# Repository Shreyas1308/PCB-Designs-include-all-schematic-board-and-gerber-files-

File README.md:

# PCB-Designs-include-all-schematic-board-and-gerber-files-
All file including Gerber(.zip), schematic and board are included here.

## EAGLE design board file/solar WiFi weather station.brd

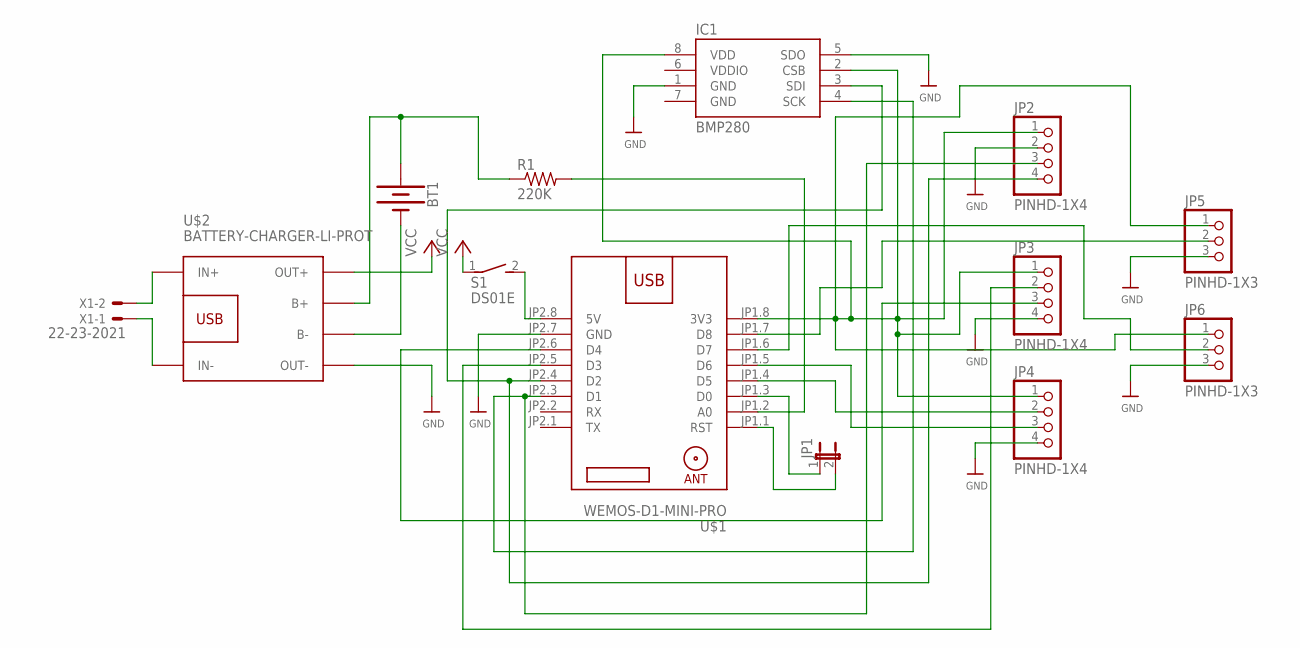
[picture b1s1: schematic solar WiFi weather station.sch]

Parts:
BT1: BATTERY-AAA
IC1: BMP280
JP1: JP1E; JP1
JP2, JP3, JP4: PINHD-1X4; 1X04
JP5, JP6: PINHD-1X3; 1X03
R1: 220K; 0204/7
S1: DS01E; DS-01
U$1: WEMOS-D1-MINI-PRO
U$2: BATTERY-CHARGER-LI-PROT
X1: 22-23-2021

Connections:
GND: IC1.1 (GND), IC1.5 (SDO), IC1.7 (GND), JP2.2, JP3.4, JP4.4, JP5.3, JP6.3, U$1.JP2.7 (GND), U$2.OUT-
unnamed: U$2.IN+, X1.2
unnamed: U$2.IN-, X1.1
unnamed: BT1.PWR@1 (+), R1.1, U$2.B+
unnamed: BT1.GND@1 (-), U$2.B-
unnamed: R1.2, U$1.JP1.2 (A0)
unnamed: JP1.1, U$1.JP1.3 (D0)
unnamed: JP1.2, U$1.JP1.1 (RST)
unnamed: S1.2, U$1.JP2.8 (5V)
unnamed: JP3.2, U$1.JP2.5 (D3)
unnamed: IC1.2 (CSB), IC1.8 (VDD), JP2.1, JP3.1, JP4.1, JP5.1, JP6.1, U$1.JP1.8 (3V3)
unnamed: IC1.4 (SCK), JP2.3, U$1.JP2.3 (D1)
unnamed: JP3.3, U$1.JP2.6 (D4)
unnamed: IC1.3 (SDI), JP2.4, U$1.JP2.4 (D2)
unnamed: JP4.2, U$1.JP1.4 (D5)
unnamed: JP4.3, U$1.JP1.5 (D6)
unnamed: JP6.2, U$1.JP1.6 (D7)
unnamed: JP5.2, U$1.JP1.7 (D8)
VCC: S1.1, U$2.OUT+

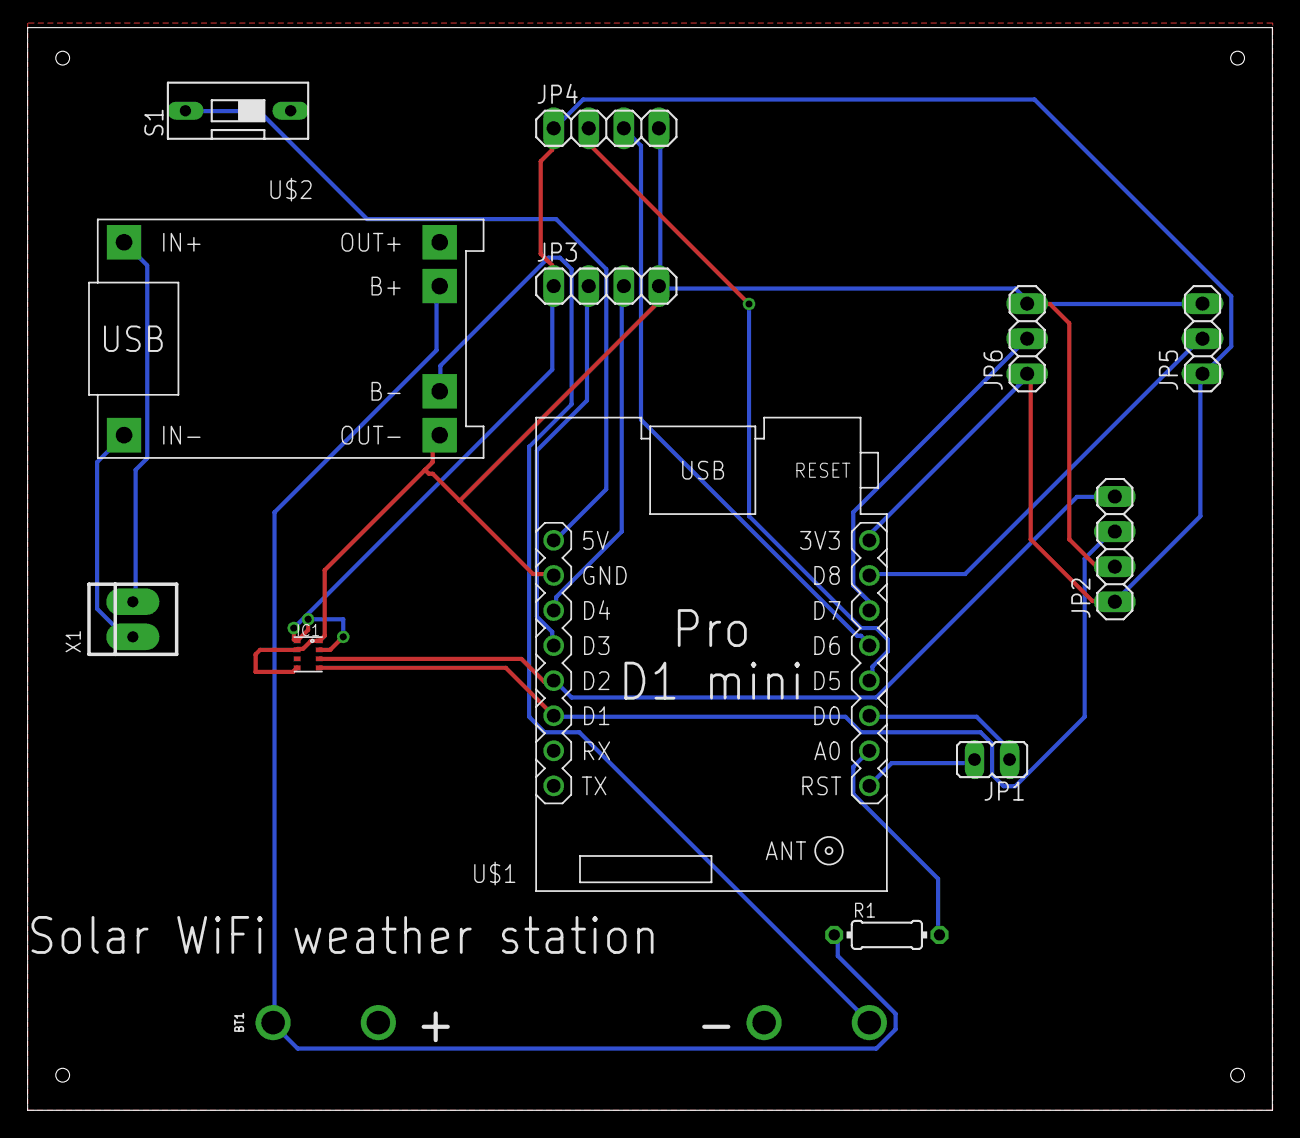
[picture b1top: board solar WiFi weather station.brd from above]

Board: 2 copper layers, 90.2 x 78.4 mm, 13 parts (0 on the bottom side), 19 nets.

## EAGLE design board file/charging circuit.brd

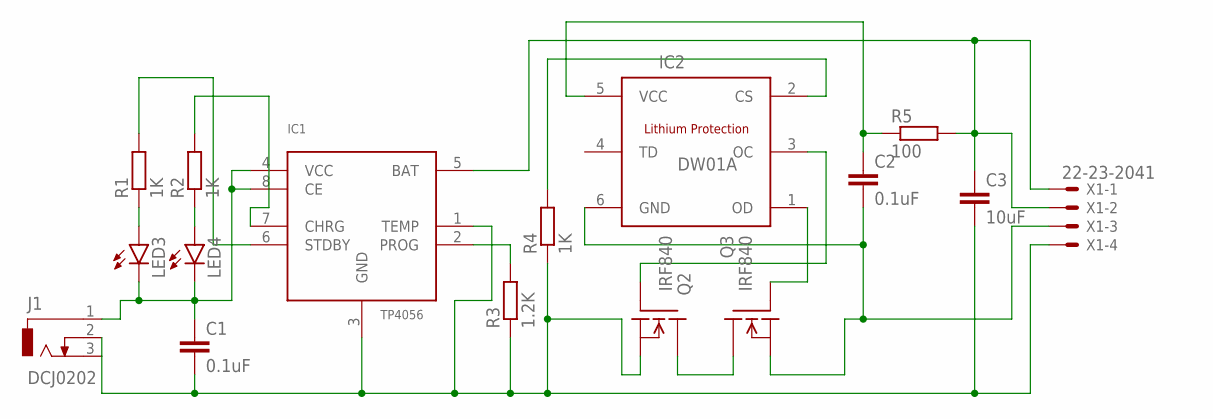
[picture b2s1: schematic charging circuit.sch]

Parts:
C1, C2: 0.1uF; C0805
C3: 10uF; C0805
IC1: TP4056; SOP-8
IC2: DW01A; SOT23-6
J1: DCJ0202
LED3, LED4: LEDCHIP-LED0805; CHIP-LED0805
Q2, Q3: IRF840; TO220
R1, R2, R4: 1K; 0207/10
R3: 1.2K; 0207/10
R5: 100; 0207/10
X1: 22-23-2041

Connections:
unnamed: C1.1, IC1.4 (VCC), IC1.8 (CE), J1.1, LED3.C, LED4.C
unnamed: C1.2, C3.2, IC1.1 (TEMP), IC1.3 (GND), J1.2, J1.3, Q2.3 (S), R3.1, R4.1, X1.4
unnamed: IC2.3 (OC), Q2.1 (G)
unnamed: LED4.A, R2.1
unnamed: LED3.A, R1.1
unnamed: IC1.6 (STDBY), R1.2
unnamed: IC1.7 (CHRG), R2.2
unnamed: IC1.2 (PROG), R3.2
unnamed: C3.1, IC1.5 (BAT), R5.2, X1.1, X1.2
unnamed: IC2.2 (CS), R4.2
unnamed: IC2.1 (OD), Q3.1 (G)
unnamed: C2.2, IC2.6 (GND), Q3.3 (S), X1.3
unnamed: C2.1, IC2.5 (VCC), R5.1
unnamed: Q2.2 (D), Q3.2 (D)

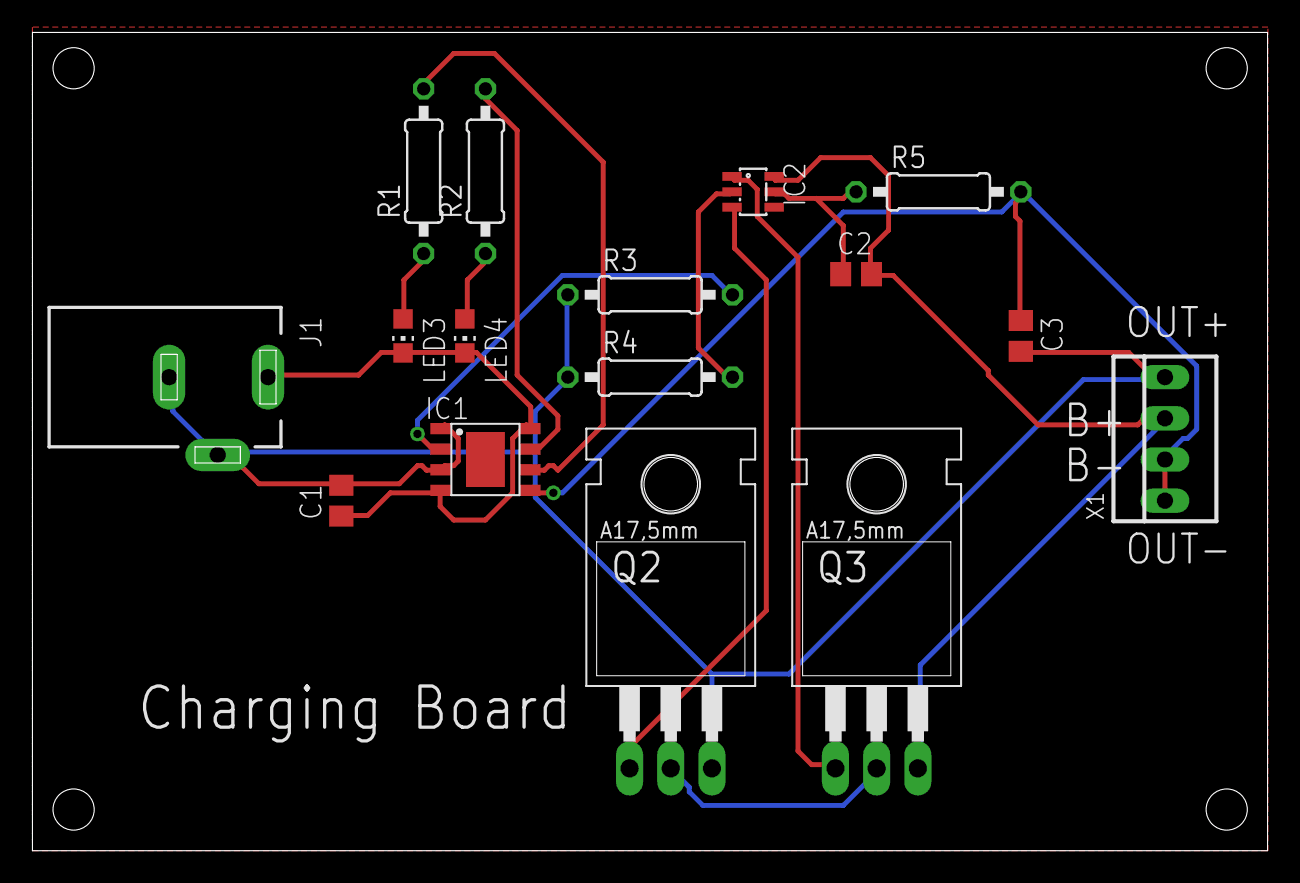
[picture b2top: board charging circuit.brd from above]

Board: 2 copper layers, 76.2 x 50.5 mm, 16 parts (0 on the bottom side), 14 nets.

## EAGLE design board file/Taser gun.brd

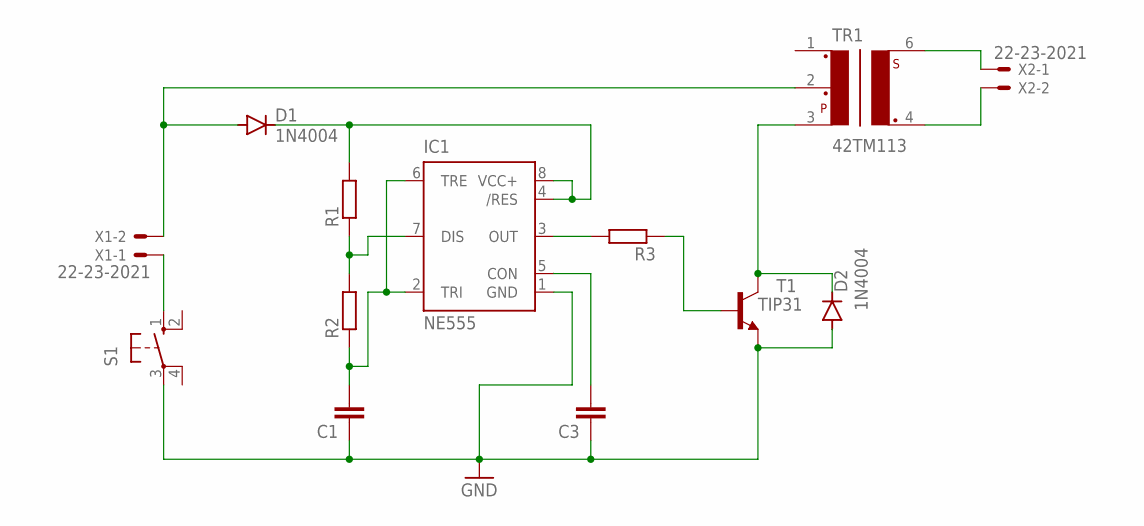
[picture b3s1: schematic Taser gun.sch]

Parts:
C1, C3: C-EU025-030X050; C025-030X050
D1, D2: 1N4004; DO41-10
IC1: NE555; DIL-08
R1, R2, R3: R-EU_0204/7; 0204/7
S1: 10-XX; B3F-10XX
T1: TIP31; TO220
TR1: 42TM113; 42TM
X1, X2: 22-23-2021

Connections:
GND: C1.1, C3.1, D2.A, IC1.1 (GND), S1.3, T1.3 (E)
unnamed: IC1.7 (DIS), R1.1, R2.2
unnamed: D1.C, IC1.4 (/RES), IC1.8 (VCC+), R1.2
unnamed: C1.2, IC1.2 (TRI), IC1.6 (TRE), R2.1
unnamed: C3.2, IC1.5 (CON)
unnamed: IC1.3 (OUT), R3.2
unnamed: R3.1, T1.1 (B)
unnamed: D2.C, T1.2 (C), TR1.3
unnamed: D1.A, TR1.2, X1.2
unnamed: S1.1 (S), X1.1
unnamed: TR1.6, X2.1
unnamed: TR1.4, X2.2

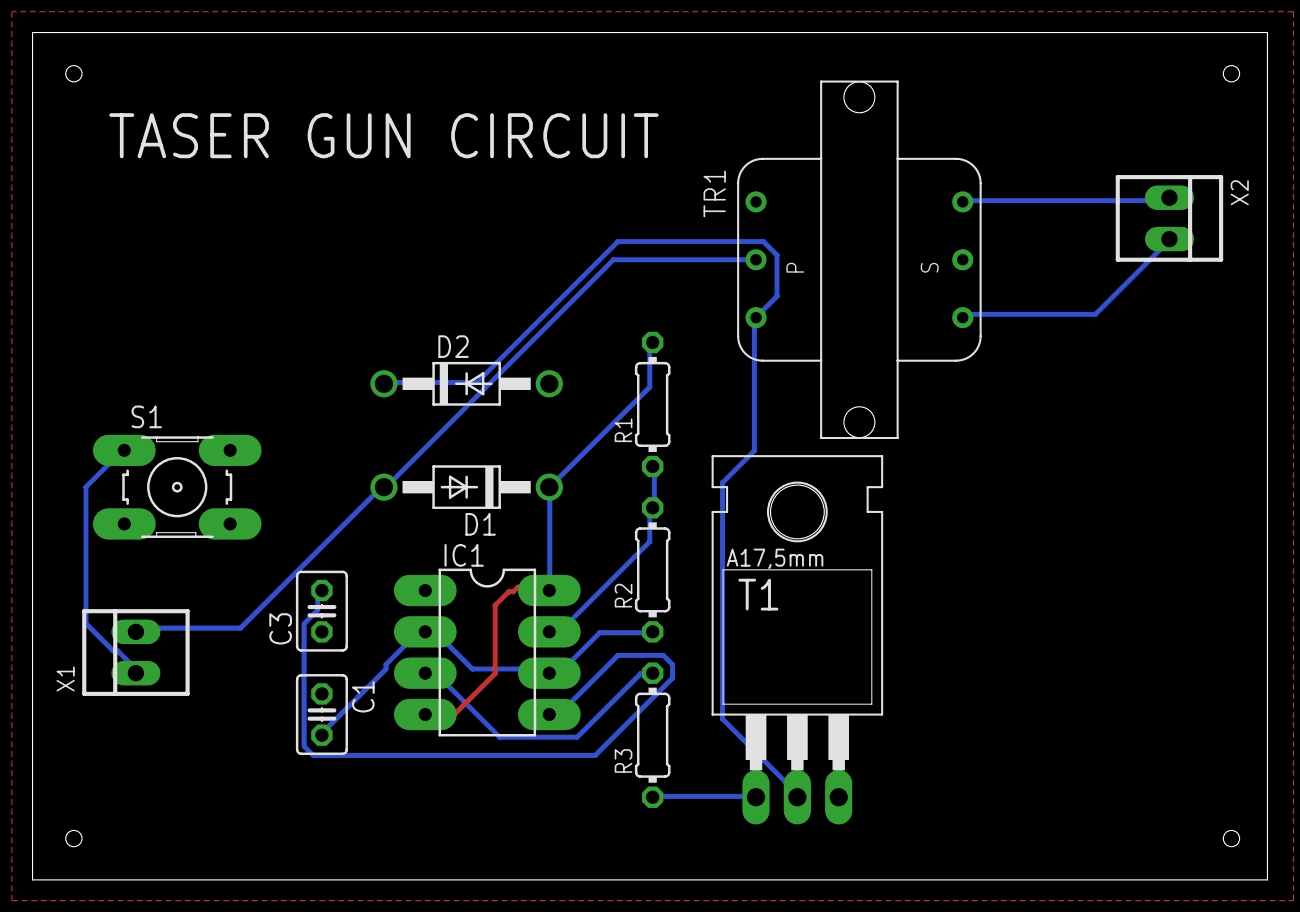
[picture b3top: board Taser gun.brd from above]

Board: 2 copper layers, 75.9 x 52.1 mm, 13 parts (0 on the bottom side), 12 nets.

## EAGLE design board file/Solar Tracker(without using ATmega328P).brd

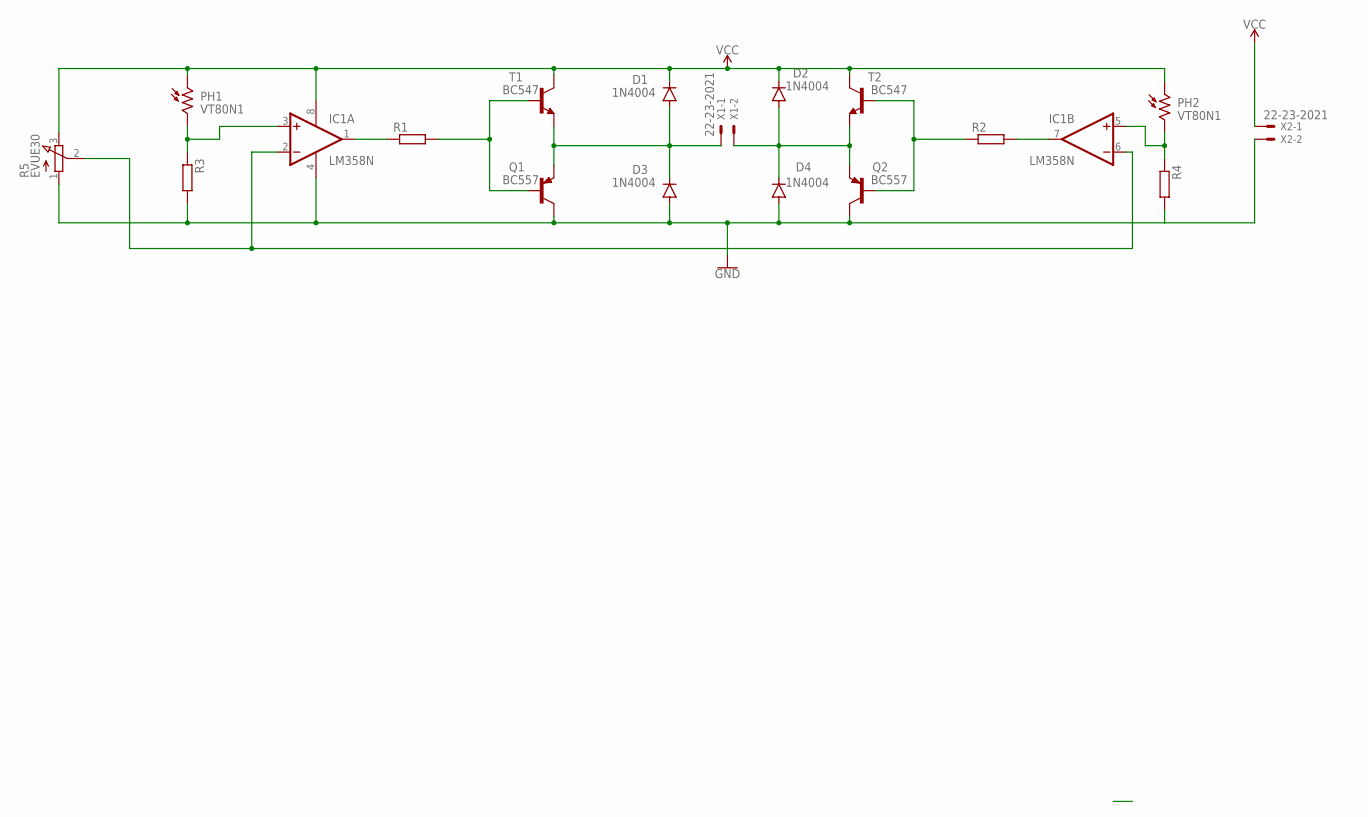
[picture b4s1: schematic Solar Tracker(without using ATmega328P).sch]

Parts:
D1, D2, D3, D4: 1N4004; DO41-10
IC1: LM358N; DIL08
PH1, PH2: VT80N1; VT800
Q1, Q2: BC557; TO92
R1, R2, R3, R4: R-EU_0204/7; 0204/7
R5: EVUE30; EVUE
T1, T2: BC547; TO92
X1, X2: 22-23-2021

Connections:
GND: D3.A, D4.A, IC1.4 (V-), Q1.3 (C), Q2.3 (C), R3.2, R4.2, R5.1 (A), X2.2
unnamed: D1.A, D3.C, Q1.1 (E), T1.1 (E), X1.1
unnamed: D2.A, D4.C, Q2.1 (E), T2.1 (E), X1.2
unnamed: Q2.2 (B), R2.1, T2.2 (B)
unnamed: Q1.2 (B), R1.2, T1.2 (B)
unnamed: IC1.5 (+IN), PH2.2, R4.1
unnamed: IC1.7 (OUT), R2.2
unnamed: IC1.1 (OUT), R1.1
unnamed: IC1.3 (+IN), PH1.2, R3.1
unnamed: IC1.2 (-IN), IC1.6 (-IN), R5.2 (S)
VCC: D1.C, D2.C, IC1.8 (V+), PH1.1, PH2.1, R5.3 (E), T1.3 (C), T2.3 (C), X2.1

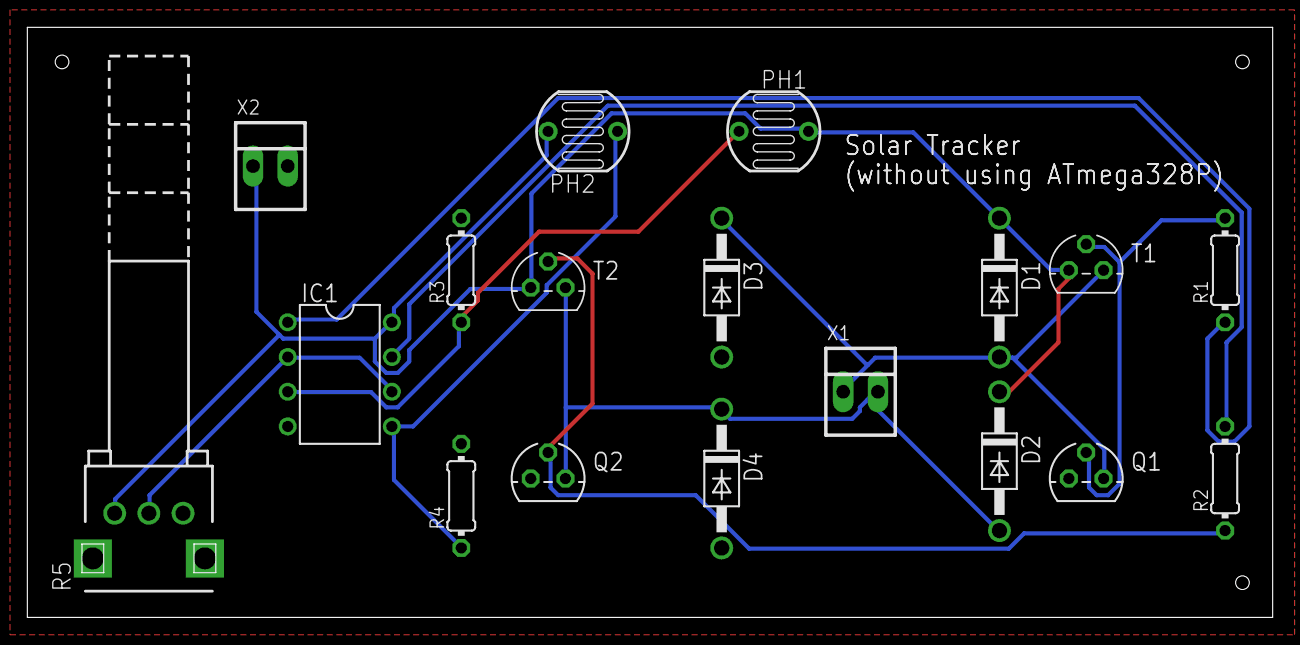
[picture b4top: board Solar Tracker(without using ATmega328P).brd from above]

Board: 2 copper layers, 91.1 x 43.2 mm, 18 parts (0 on the bottom side), 11 nets.

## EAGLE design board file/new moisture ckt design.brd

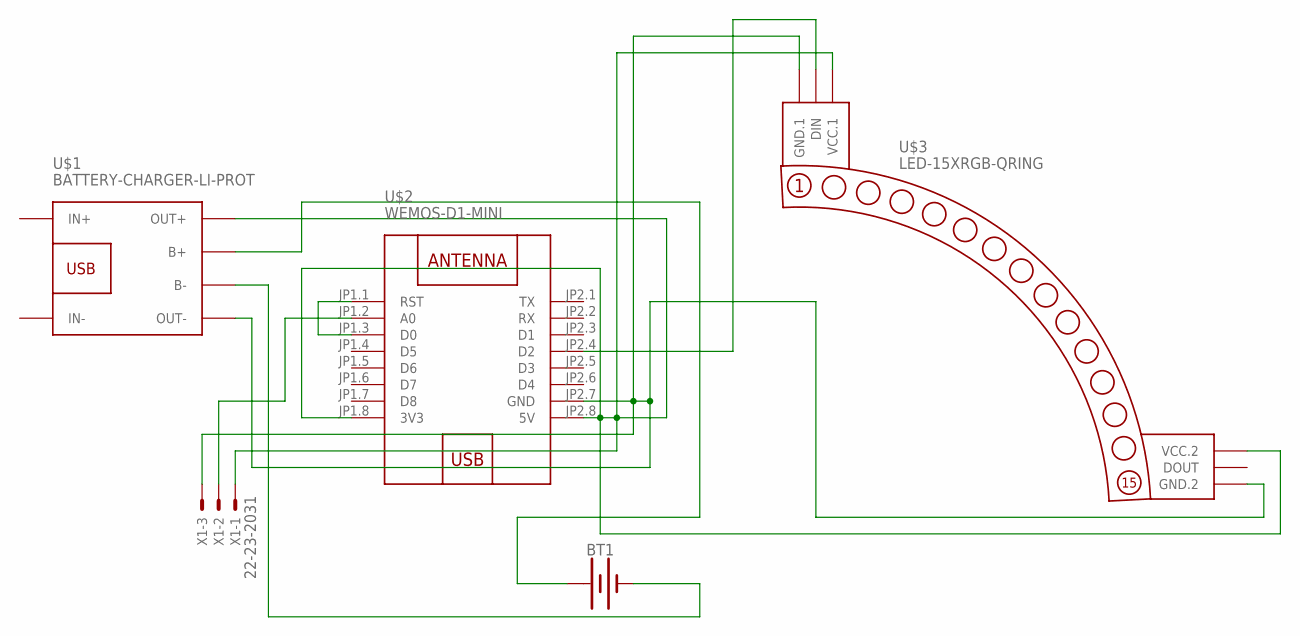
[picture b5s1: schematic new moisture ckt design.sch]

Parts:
BT1: BATTERY-12MM_PTH; BATTCON_12MM_PTH
U$1: BATTERY-CHARGER-LI-PROT
U$2: WEMOS-D1-MINI
U$3: LED-15XRGB-QRING
X1: 22-23-2031

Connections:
unnamed: U$2.JP1.1 (RST), U$2.JP1.3 (D0)
unnamed: U$2.JP1.2 (A0), X1.2
unnamed: U$1.OUT+, U$2.JP1.8 (3V3), U$2.JP2.8 (5V), U$3.3 (VCC.1), U$3.6 (VCC.2), X1.1
unnamed: U$1.OUT-, U$2.JP2.7 (GND), U$3.1 (GND.1), U$3.4 (GND.2), X1.3
unnamed: BT1.GND (-), U$1.B-
unnamed: BT1.VCC@1 (+), U$1.B+
unnamed: U$2.JP2.4 (D2), U$3.2 (DIN)

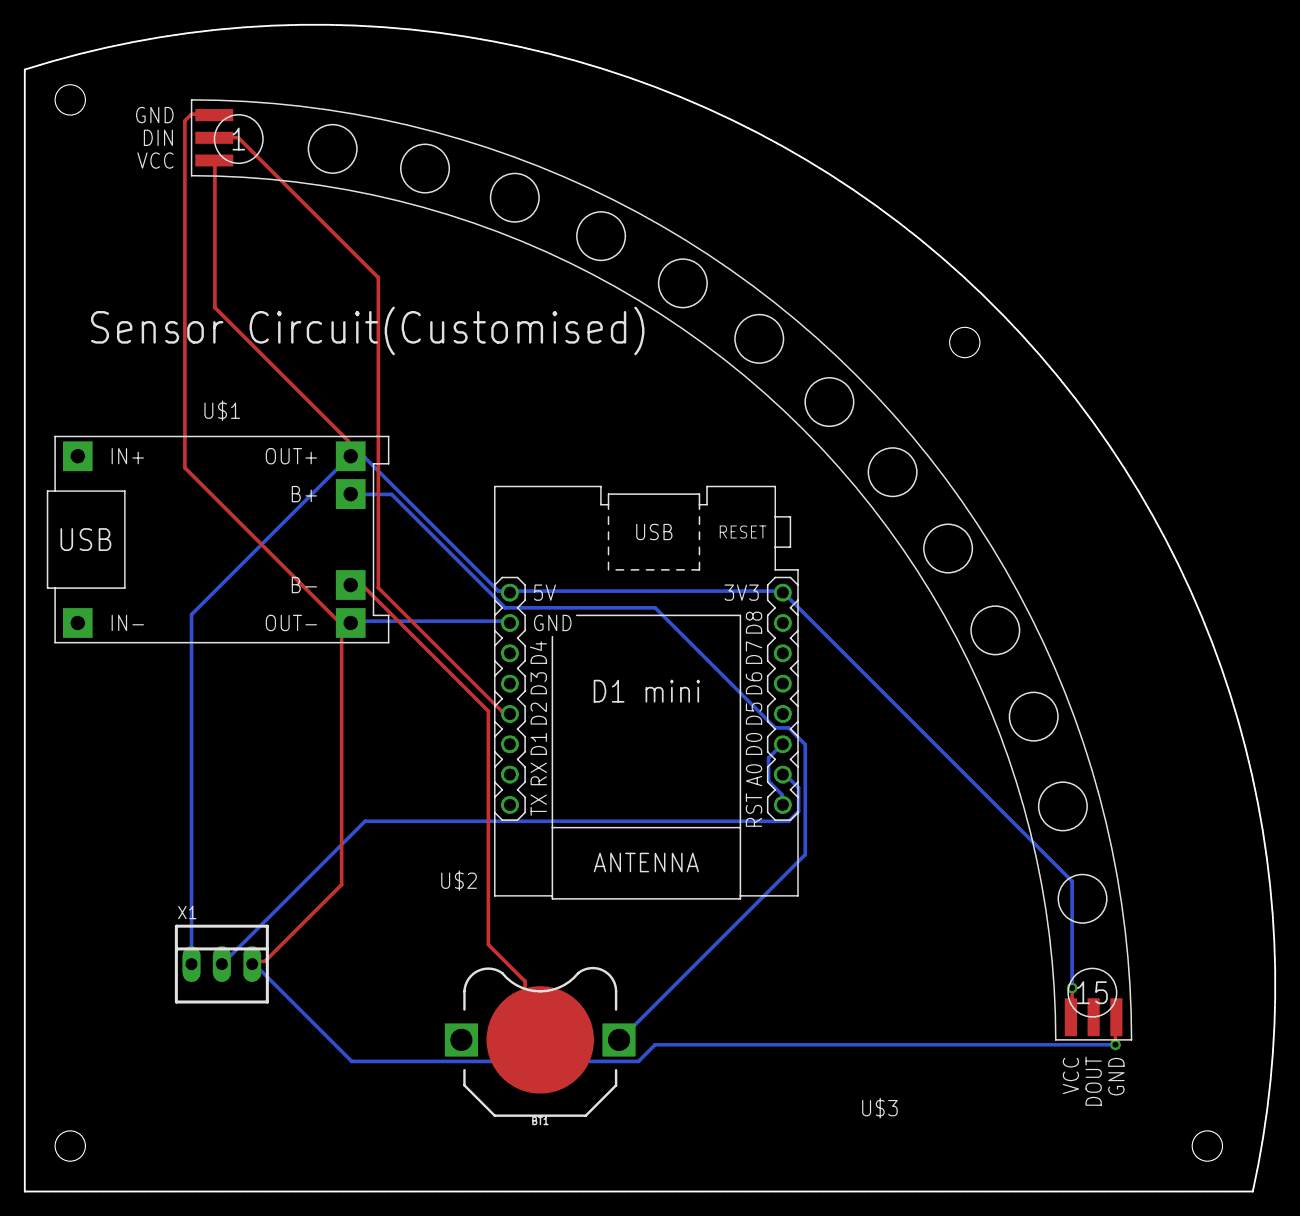
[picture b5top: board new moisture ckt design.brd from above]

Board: 2 copper layers, 104.7 x 97.7 mm, 5 parts (0 on the bottom side), 7 nets.

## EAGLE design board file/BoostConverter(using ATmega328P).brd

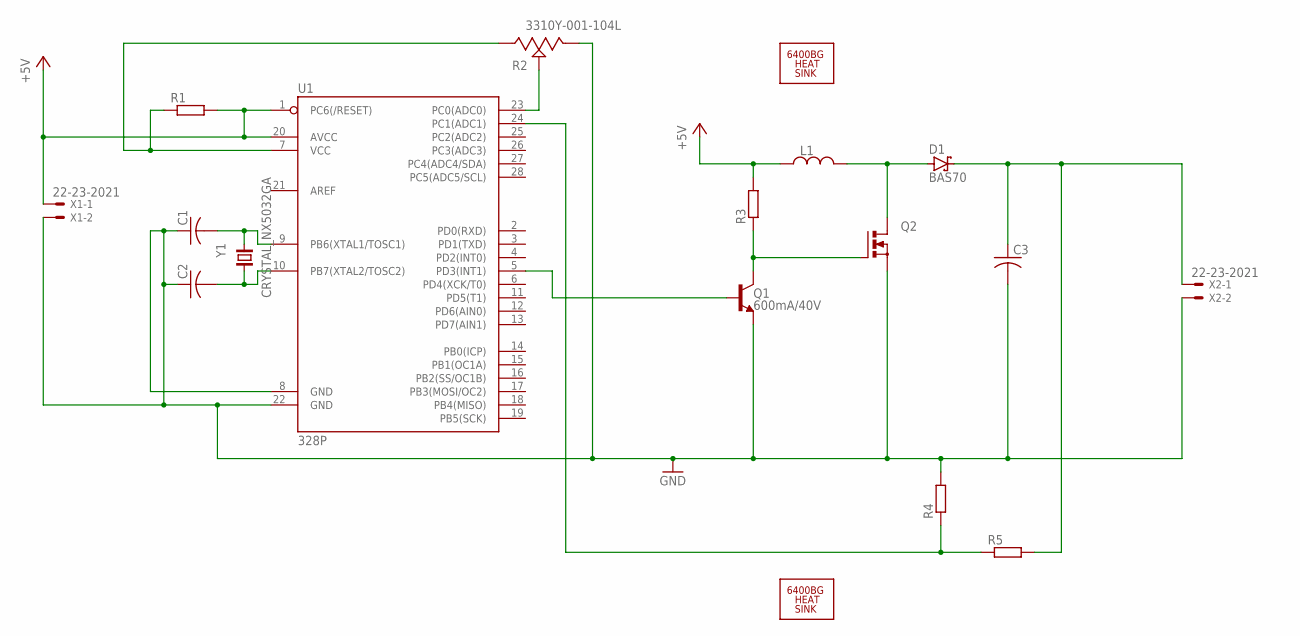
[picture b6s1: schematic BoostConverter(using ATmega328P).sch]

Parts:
C1, C2, C3: C-USC0805; C0805
D1: BAS70; SOT23
H1, H2: 6400BG_HEATSINK
L1: L_CHIP(4509-METRIC); INDC4509X190
Q1: 600mA/40V; SOT23-3
Q2: N-MOSFET-SO8S; SO-08
R1: R-EU_R0805; R0805
R2: 3310Y-001-104L; 3310Y-001-104L-ND
R3: R-EU_M1406; M1406
R4, R5: R-EU_M0805; M0805
U1: 328P; DIP28
X1, X2: 22-23-2021
Y1: CRYSTAL_NX5032GA; CRYSTAL_2-SMD-5X3

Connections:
+5V: L1.1, R1.2, R3.2, U1.1 (PC6(/RESET)), U1.20 (AVCC), X1.1
GND: C1.1, C2.1, C3.2, Q1.2 (E), Q2.1 (S), Q2.2 (S), Q2.3 (S), R2.1, R4.2, U1.8 (GND), U1.22 (GND), X1.2, X2.2
unnamed: C1.2, U1.9 (PB6(XTAL1/TOSC1)), Y1.2
unnamed: C2.2, U1.10 (PB7(XTAL2/TOSC2)), Y1.1
unnamed: R4.1, R5.1, U1.24 (PC1(ADC1))
unnamed: Q1.3 (C), Q2.4 (G), R3.1
unnamed: R2.2, U1.23 (PC0(ADC0))
unnamed: Q1.1 (B), U1.5 (PD3(INT1))
unnamed: D1.1 (A), L1.2, Q2.5 (D), Q2.6 (D), Q2.7 (D), Q2.8 (D)
unnamed: C3.1, D1.3 (C), R5.2, X2.1
unnamed: R1.1, R2.3, U1.7 (VCC)

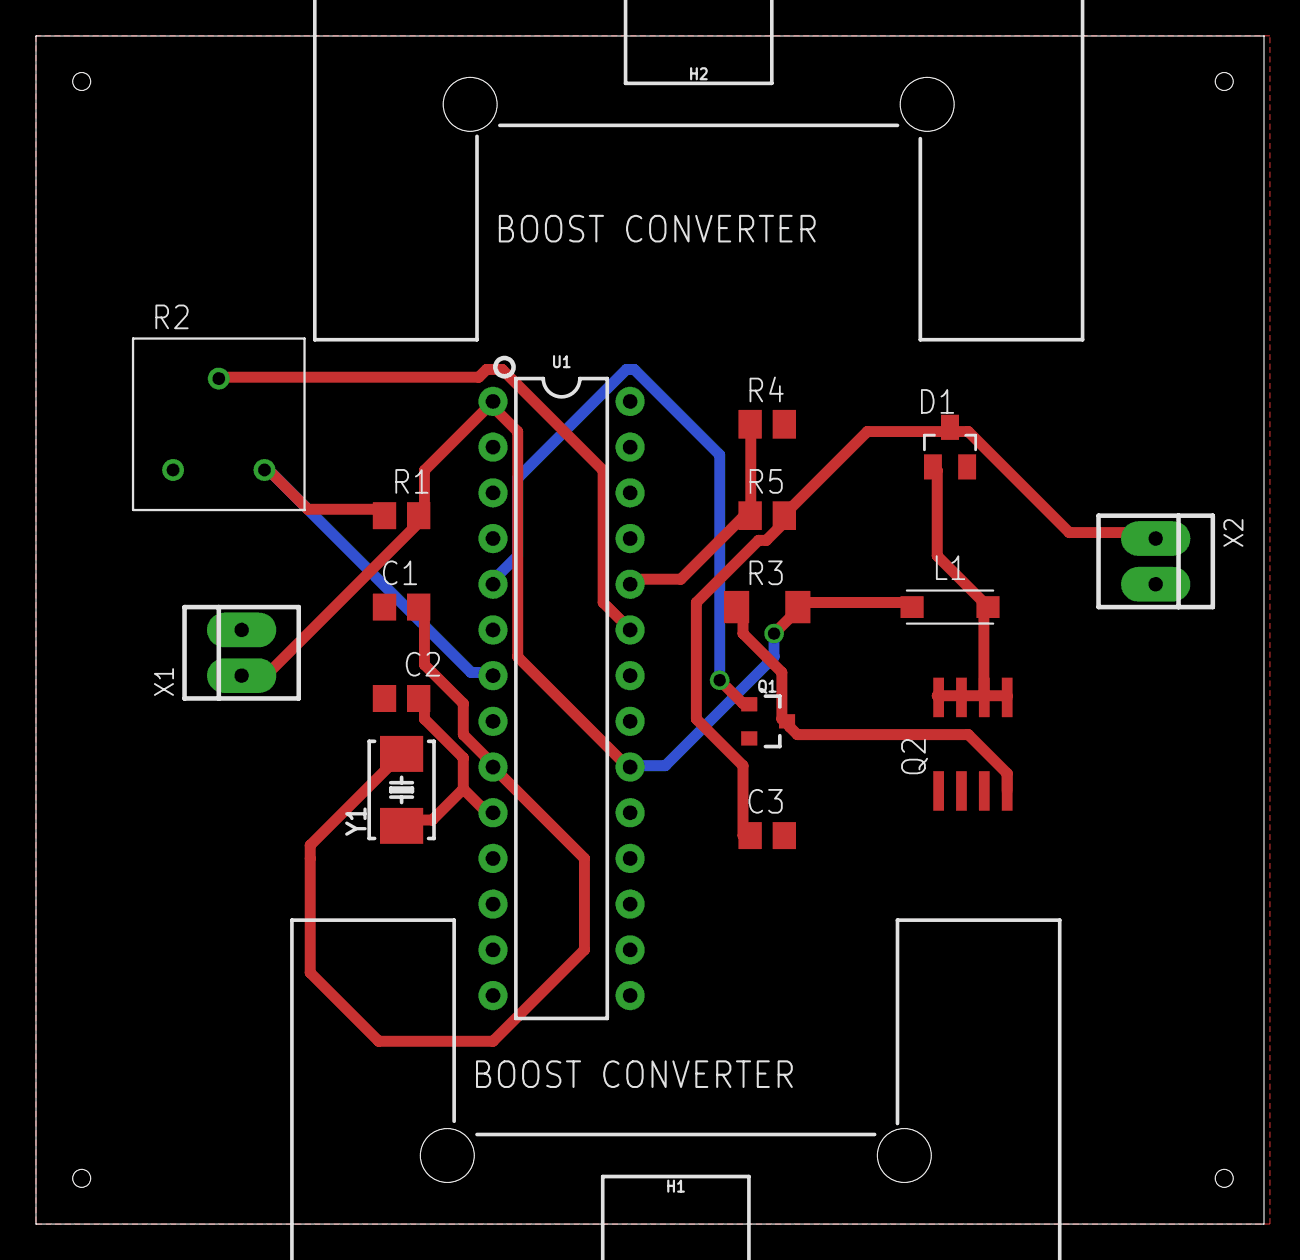
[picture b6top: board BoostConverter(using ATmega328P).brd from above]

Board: 2 copper layers, 68.2 x 66.0 mm, 18 parts (0 on the bottom side), 11 nets.

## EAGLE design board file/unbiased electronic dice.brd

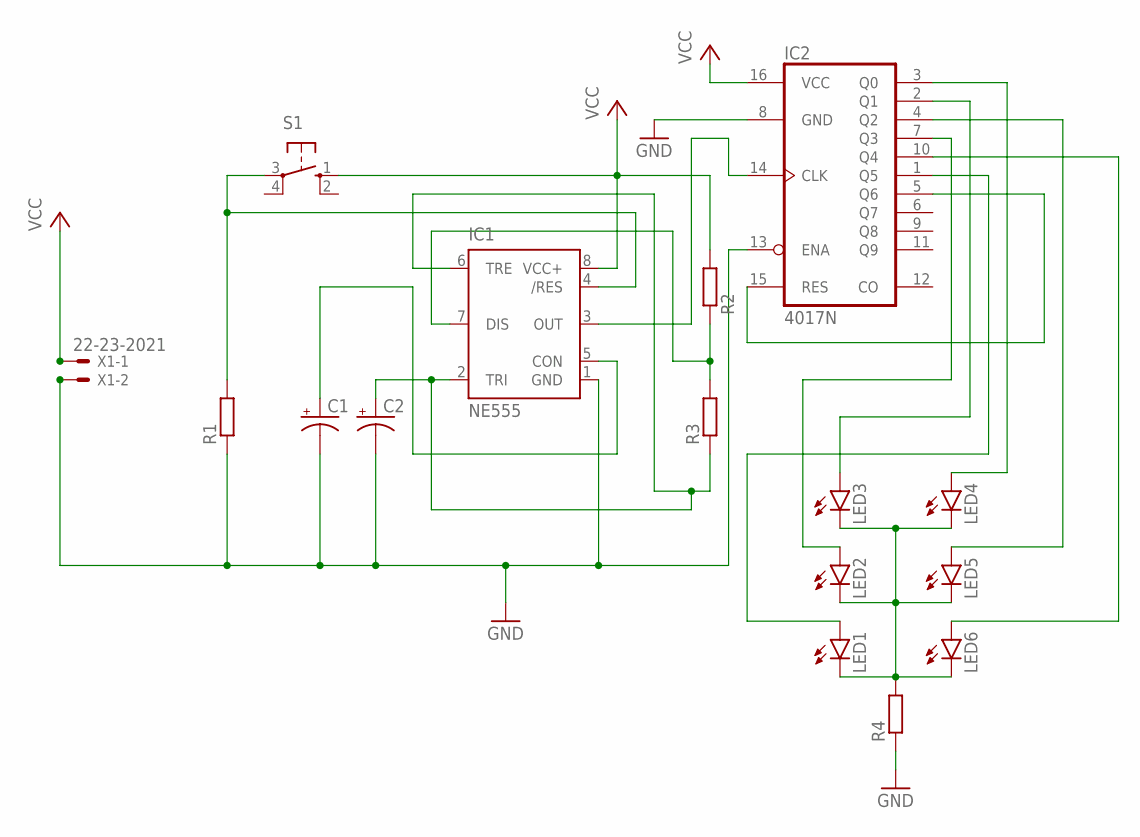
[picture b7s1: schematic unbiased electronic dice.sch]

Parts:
C1, C2: CPOL-USE2,5-6E; E2,5-6E
IC1: NE555; DIL-08
IC2: 4017N; DIL16
LED1, LED2, LED3, LED4, LED5, LED6: LED5MM
R1, R2, R3: R-EU_0207/15; 0207/15; MPN MS27474E20F16P
R4: R-EU_0207/7; 0207/7
S1: 10-XX; B3F-10XX
X1: 22-23-2021

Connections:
GND: C1.-, C2.-, IC1.1 (GND), IC2.8 (GND), IC2.13 (ENA), R1.1, R4.1, X1.2
unnamed: IC1.7 (DIS), R2.1, R3.2
unnamed: IC1.3 (OUT), IC2.14 (CLK)
unnamed: IC1.4 (/RES), R1.2, S1.3
unnamed: C1.+, IC1.5 (CON)
unnamed: C2.+, IC1.2 (TRI), IC1.6 (TRE), R3.1
unnamed: IC2.3 (Q0), LED4.A
unnamed: IC2.2 (Q1), LED3.A
unnamed: IC2.4 (Q2), LED5.A
unnamed: IC2.7 (Q3), LED2.A
unnamed: IC2.10 (Q4), LED6.A
unnamed: IC2.1 (Q5), LED1.A
unnamed: IC2.5 (Q6), IC2.15 (RES)
unnamed: LED1.K (C), LED2.K (C), LED3.K (C), LED4.K (C), LED5.K (C), LED6.K (C), R4.2
VCC: IC1.8 (VCC+), IC2.16 (VCC), R2.2, S1.1 (S), X1.1

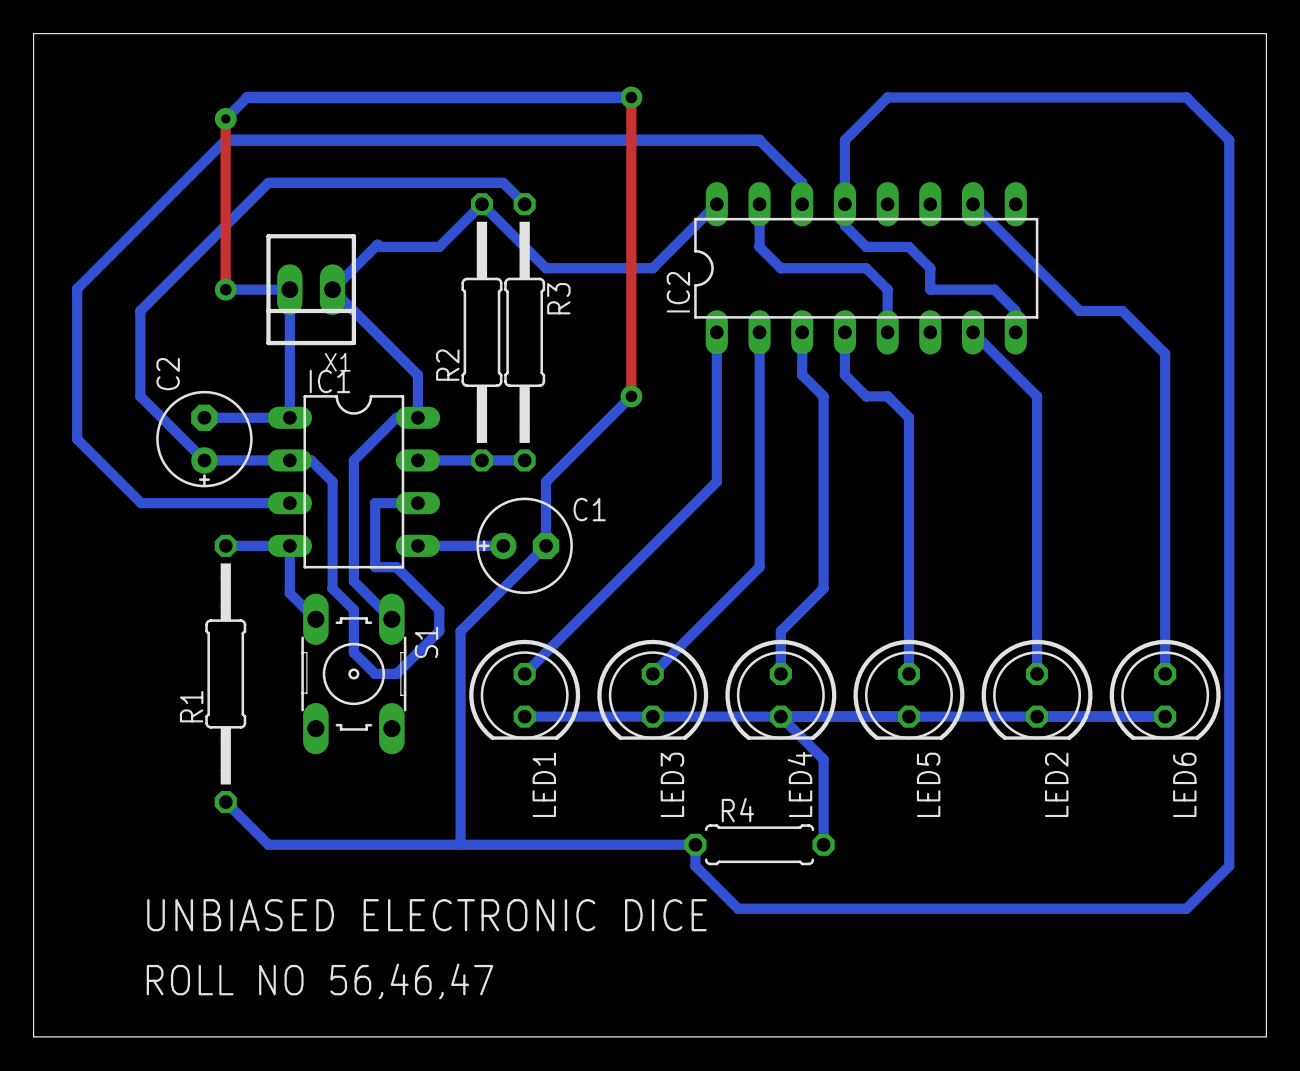
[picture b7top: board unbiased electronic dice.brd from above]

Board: 2 copper layers, 73.3 x 59.7 mm, 16 parts (0 on the bottom side), 15 nets.

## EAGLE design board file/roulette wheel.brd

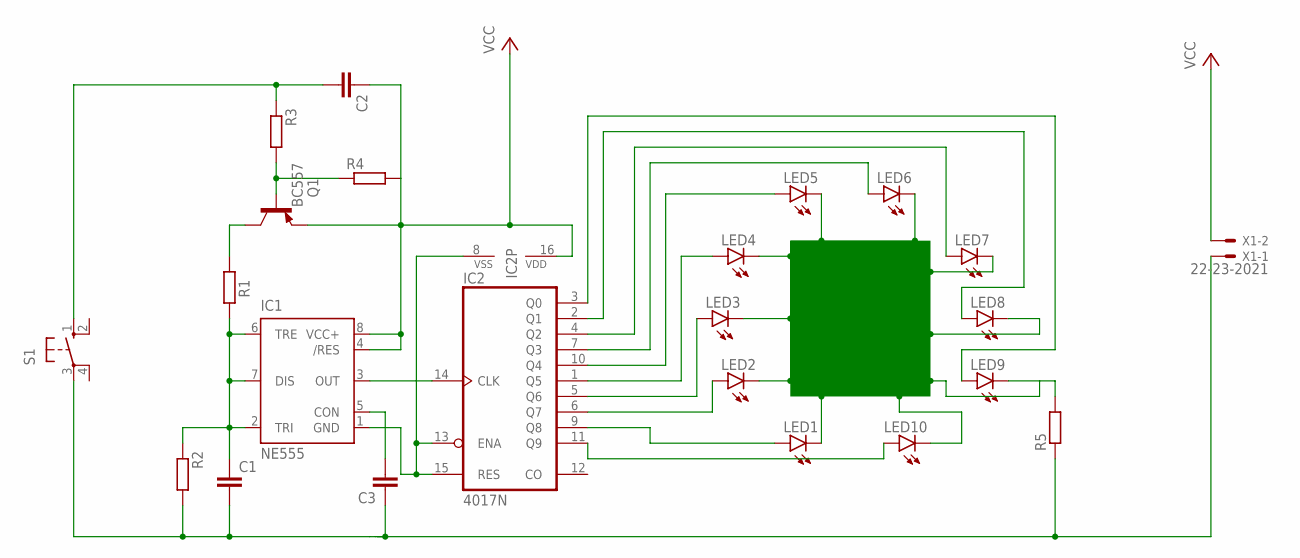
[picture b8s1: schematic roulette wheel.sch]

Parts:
C1, C2, C3: C-EU025-024X044; C025-024X044
IC1: NE555; DIL-08
IC2: 4017N; DIL16
LED1, LED2, LED3, LED4, LED5, LED6, LED7, LED8, LED9, LED10: LED3MM
Q1: BC557; TO92
R1, R2, R3, R4, R5: R-EU_0204/7; 0204/7
S1: 10-XX; B3F-10XX
X1: 22-23-2021

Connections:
unnamed: C1.1, IC1.2 (TRI), IC1.6 (TRE), IC1.7 (DIS), R1.2, R2.1
unnamed: IC1.3 (OUT), IC2.14 (CLK)
unnamed: Q1.3 (C), R1.1
unnamed: Q1.2 (B), R3.2, R4.1
unnamed: C2.2, R3.1, S1.1 (S)
unnamed: IC2.9 (Q8), LED1.A
unnamed: IC2.8 (VSS), IC2.13 (ENA), IC2.15 (RES)
unnamed: IC2.6 (Q7), LED2.A
unnamed: IC2.5 (Q6), LED3.A
unnamed: IC2.1 (Q5), LED4.A
unnamed: IC2.10 (Q4), LED5.A
unnamed: IC2.7 (Q3), LED6.A
unnamed: IC2.4 (Q2), LED7.A
unnamed: IC2.2 (Q1), LED8.A
unnamed: IC2.3 (Q0), LED9.A
unnamed: IC2.11 (Q9), LED10.A
unnamed: LED9.K (C), R5.2
unnamed: C1.2, C3.1, R2.2, R5.1, S1.3, X1.1
unnamed: C3.2, IC1.5 (CON)
VCC: C2.1, IC1.4 (/RES), IC1.8 (VCC+), IC2.16 (VDD), Q1.1 (E), R4.2, X1.2

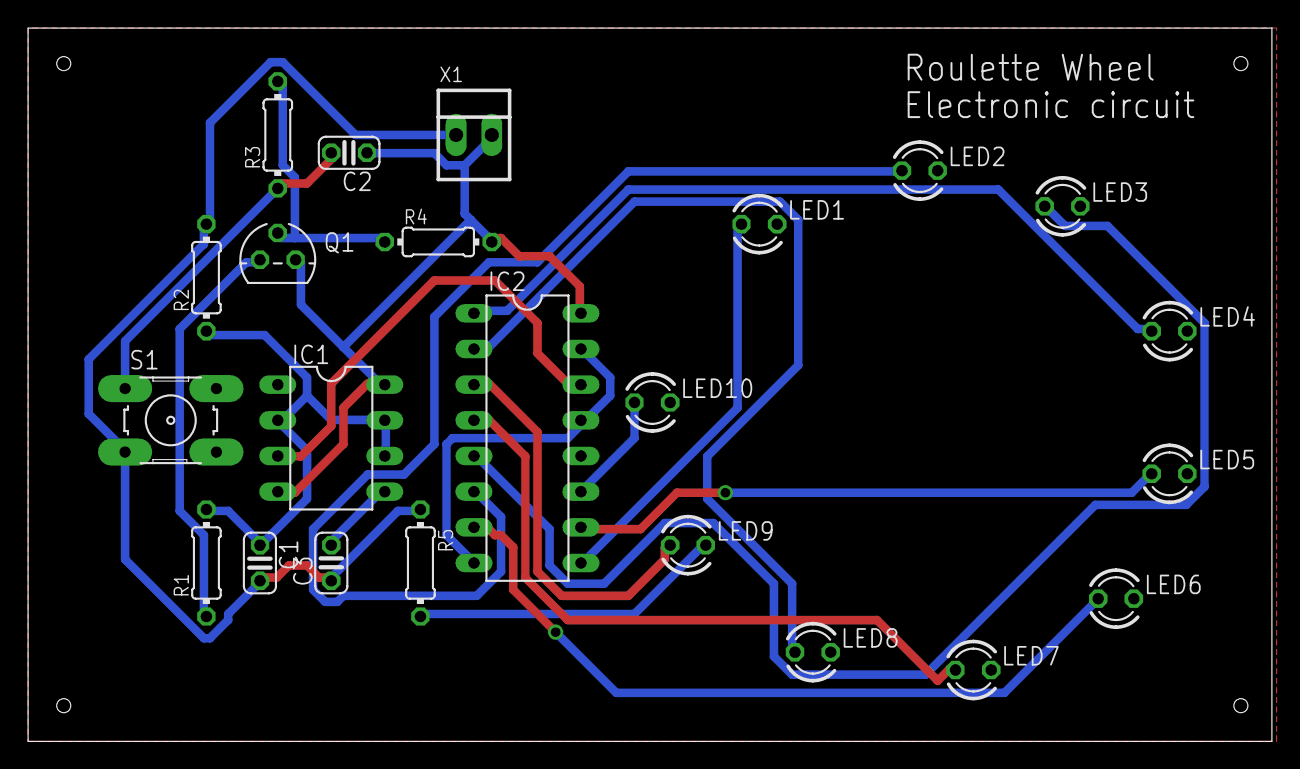
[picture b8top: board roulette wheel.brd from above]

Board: 2 copper layers, 88.6 x 50.8 mm, 23 parts (0 on the bottom side), 20 nets.

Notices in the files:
parts and their libraries:
SparkFun-IC-Microcontroller: Licensing: Creative Commons ShareAlike 4.0 International - https://creativecommons.org/licenses/by-sa/4.0
diy-modules: Released under the Creative Commons Attribution 4.0 International License: http://creativecommons.org/licenses/by/4.0
